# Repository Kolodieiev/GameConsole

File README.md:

Дякую за натхнення проєкту [Лілка v2]([./img/v21.jpg](https://github.com/and3rson/lilka))!

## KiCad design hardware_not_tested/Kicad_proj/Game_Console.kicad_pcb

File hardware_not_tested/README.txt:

Проєкт консолі для ручного виготовлення оптичним лазером або утюжною технологією. Кнопки розміщуються окремо від основної плати на корпусі.
Розмір плати 90*90мм. Теоретична товщина пристрою в корпусі - 35-40мм.

Наразі плата НЕ ТЕСТУВАЛАСЬ!

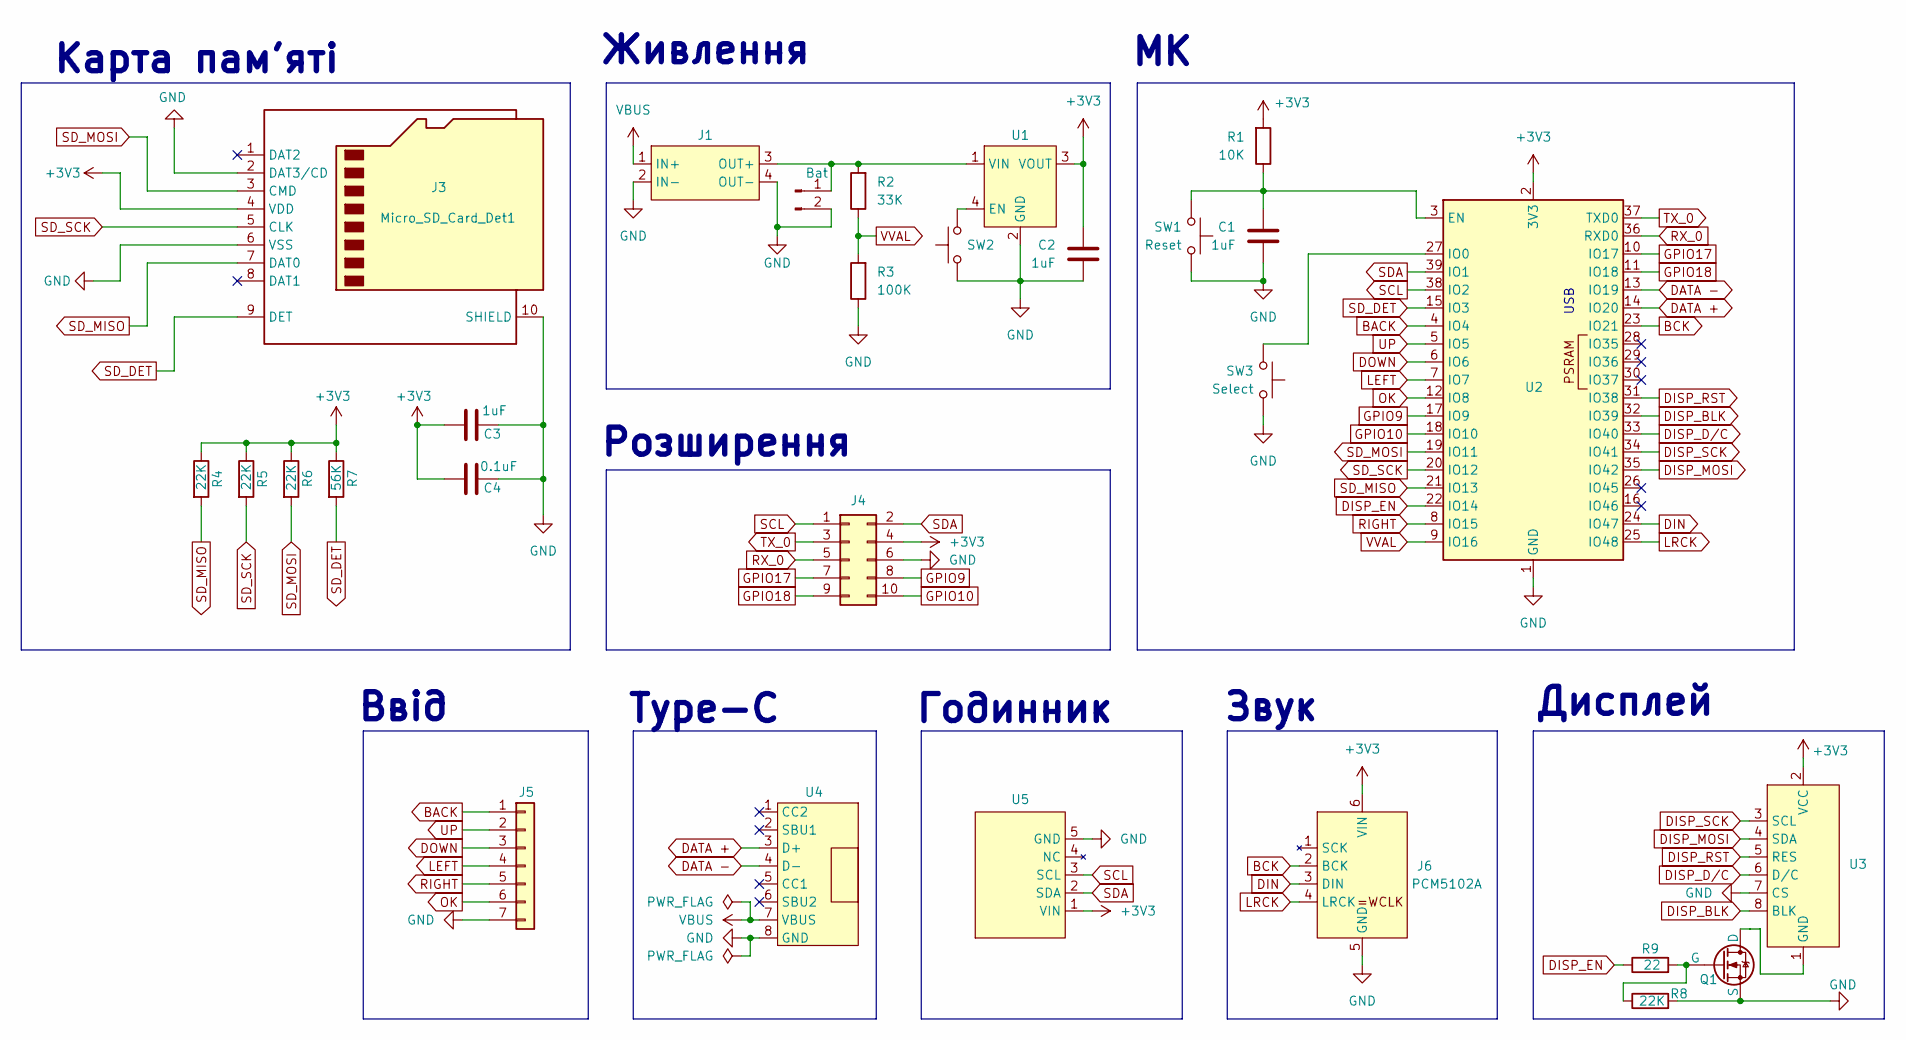
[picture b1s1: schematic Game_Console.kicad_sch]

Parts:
C1, C2, C3: 1uF; C_1206_3216Metric
C4: 0.1uF; C_1206_3216Metric
J1: Charge_Controller_TP4056_WO_Protect
J2: Bat; PinHeader_1x02_P2.54mm_Vertical
J3: Micro_SD_Card_Det1; J_SD_Card-micro_socket_A
J4: Conn_02x05_Odd_Even; PinHeader_2x05_P2.54mm_Vertical
J5: Conn_01x07; PinHeader_1x07_P2.54mm_Vertical
J6: PCM5102A; PCM5102A-I2S-Module
Q1: NMOS; SOT-23
R1: 10K; R_Axial_DIN0204_L3.6mm_D1.6mm_P7.62mm_Horizontal
R2: 33K; R_Axial_DIN0204_L3.6mm_D1.6mm_P7.62mm_Horizontal
R3: 100K; R_Axial_DIN0204_L3.6mm_D1.6mm_P7.62mm_Horizontal
R4, R5, R6, R8: 22K; R_1206_3216Metric
R7: 56K; R_1206_3216Metric
R9: 22; R_1206_3216Metric
SW1: Reset; SW_PUSH_6mm
SW2: SW_Push; PinHeader_1x02_P2.54mm_Vertical
SW3: Select; SW_PUSH_6mm
U1: xl63070_back/boost_module; XL63070_module
U2: ESP32-S3-WROOM-1
U3: IPS_240x320_2_inch
U4: USB TYPE-C to PCB; Connector_Type_C
U5: DS3231SN_module

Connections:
+3V3: C2.1, C3.1, C4.1, J3.4 (VDD), J4.4, J6.6 (VIN), R1.2, R4.1, R5.1, R6.1, R7.1, U1.3 (VOUT), U2.2 (3V3), U3.2 (VCC), U5.1 (VIN)
BACK: J5.1, U2.4 (IO4)
BCK: J6.2 (BCK), U2.23 (IO21)
DATA +: U2.14 (IO20), U4.3 (D+)
DATA -: U2.13 (IO19), U4.4 (D-)
DIN: J6.3 (DIN), U2.24 (IO47)
DISP_BLK: U2.32 (IO39), U3.8 (BLK)
DISP_D/C: U2.33 (IO40), U3.6 (D/C)
DISP_EN: R9.1, U2.22 (IO14)
DISP_MOSI: U2.35 (IO42), U3.4 (SDA)
DISP_RST: U2.31 (IO38), U3.5 (RES)
DISP_SCK: U2.34 (IO41), U3.3 (SCL)
DOWN: J5.3, U2.6 (IO6)
GND: C1.2, C2.2, C3.2, C4.2, J1.2 (IN-), J1.4 (OUT-), J2.2, J3.2 (DAT3/CD), J3.6 (VSS), J3.10 (SHIELD), J4.6, J5.7, J6.5 (GND), Q1.2 (S), R3.1, R8.2, SW1.1, SW2.1, SW3.1, U1.2 (GND), U2.1 (GND), U2.40 (GND), U2.41 (GND), U3.7 (CS), U4.8 (GND), U5.5 (GND)
GPIO9: J4.8, U2.17 (IO9)
GPIO10: J4.10, U2.18 (IO10)
GPIO17: J4.7, U2.10 (IO17)
GPIO18: J4.9, U2.11 (IO18)
LEFT: J5.4, U2.7 (IO7)
LRCK: J6.4 (LRCK), U2.25 (IO48)
unnamed: J1.3 (OUT+), J2.1, R2.2, U1.1 (VIN)
unnamed: Q1.3 (D), U3.1 (GND)
unnamed: Q1.1 (G), R8.1, R9.2
unnamed: SW2.2, U1.4 (EN)
unnamed: C1.1, R1.1, SW1.2, U2.3 (EN)
unnamed: SW3.2, U2.27 (IO0)
OK: J5.6, U2.12 (IO8)
RIGHT: J5.5, U2.8 (IO15)
RX_0: J4.5, U2.36 (RXD0)
SCL: J4.1, U2.38 (IO2), U5.3 (SCL)
SDA: J4.2, U2.39 (IO1), U5.2 (SDA)
SD_DET: J3.9 (DET), R7.2, U2.15 (IO3)
SD_MISO: J3.7 (DAT0), R4.2, U2.21 (IO13)
SD_MOSI: J3.3 (CMD), R6.2, U2.19 (IO11)
SD_SCK: J3.5 (CLK), R5.2, U2.20 (IO12)
TX_0: J4.3, U2.37 (TXD0)
UP: J5.2, U2.5 (IO5)
VBUS: J1.1 (IN+), U4.7 (VBUS)
VVAL: R2.1, R3.2, U2.9 (IO16)

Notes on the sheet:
Карта пам'яті
Годинник
USB
Дисплей
Звук
Розширення
Ввід
Type-C
Живлення

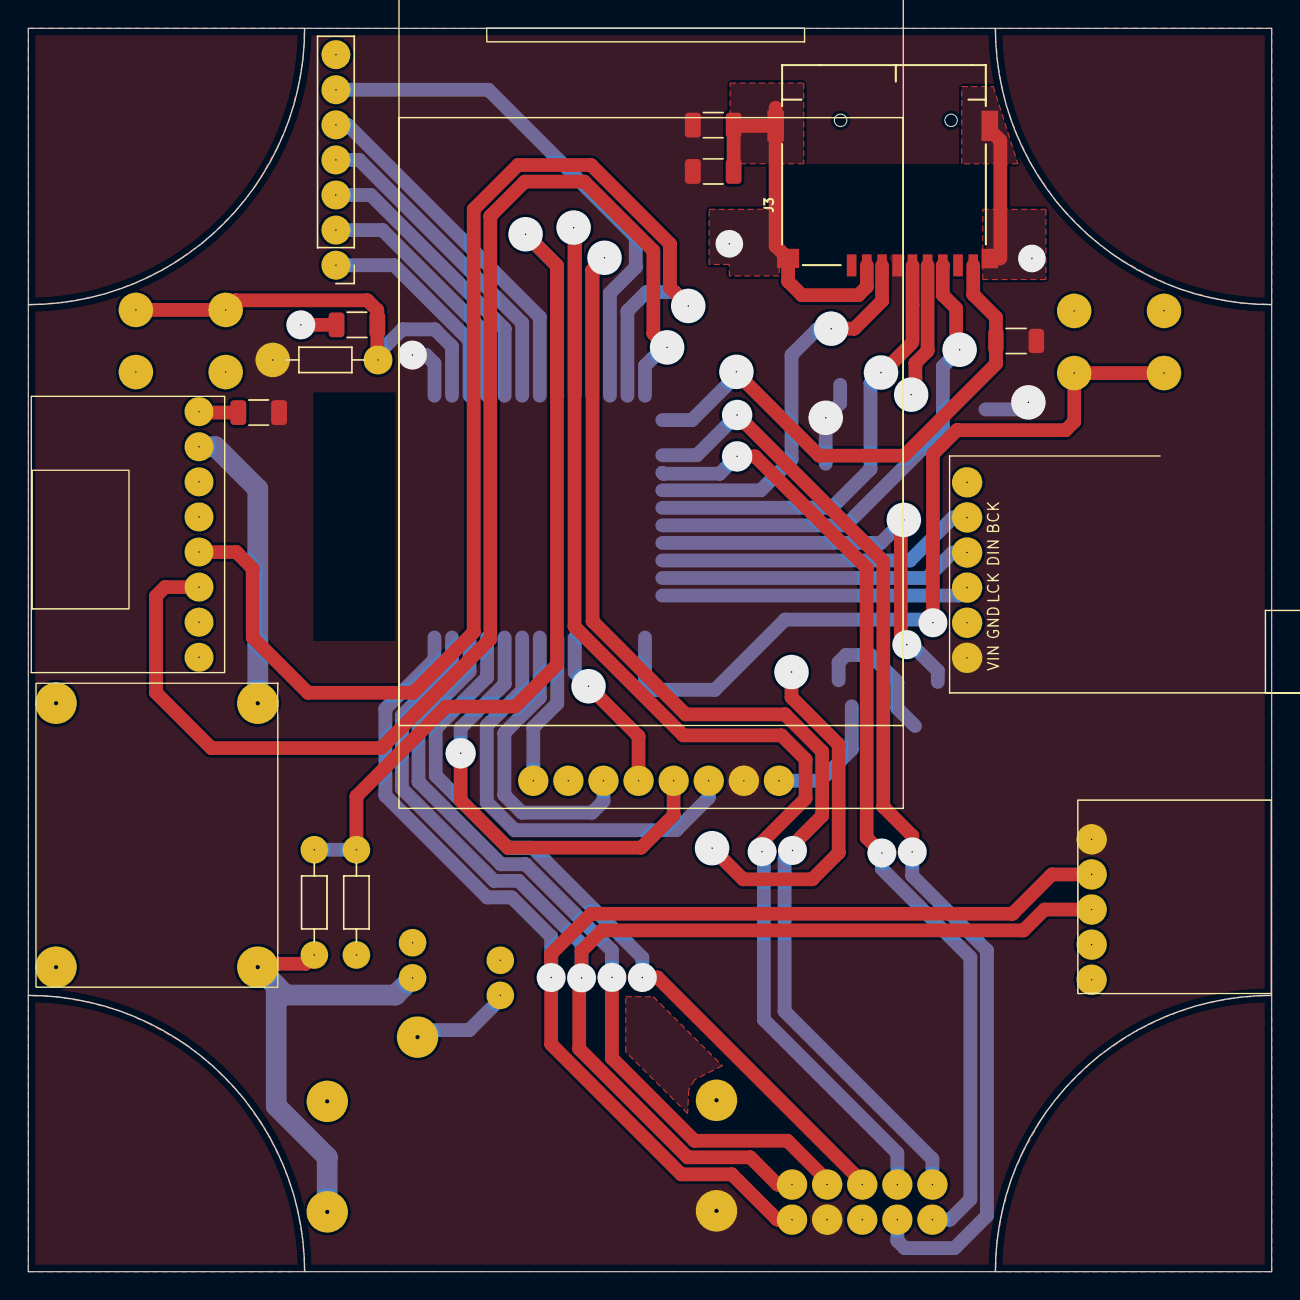
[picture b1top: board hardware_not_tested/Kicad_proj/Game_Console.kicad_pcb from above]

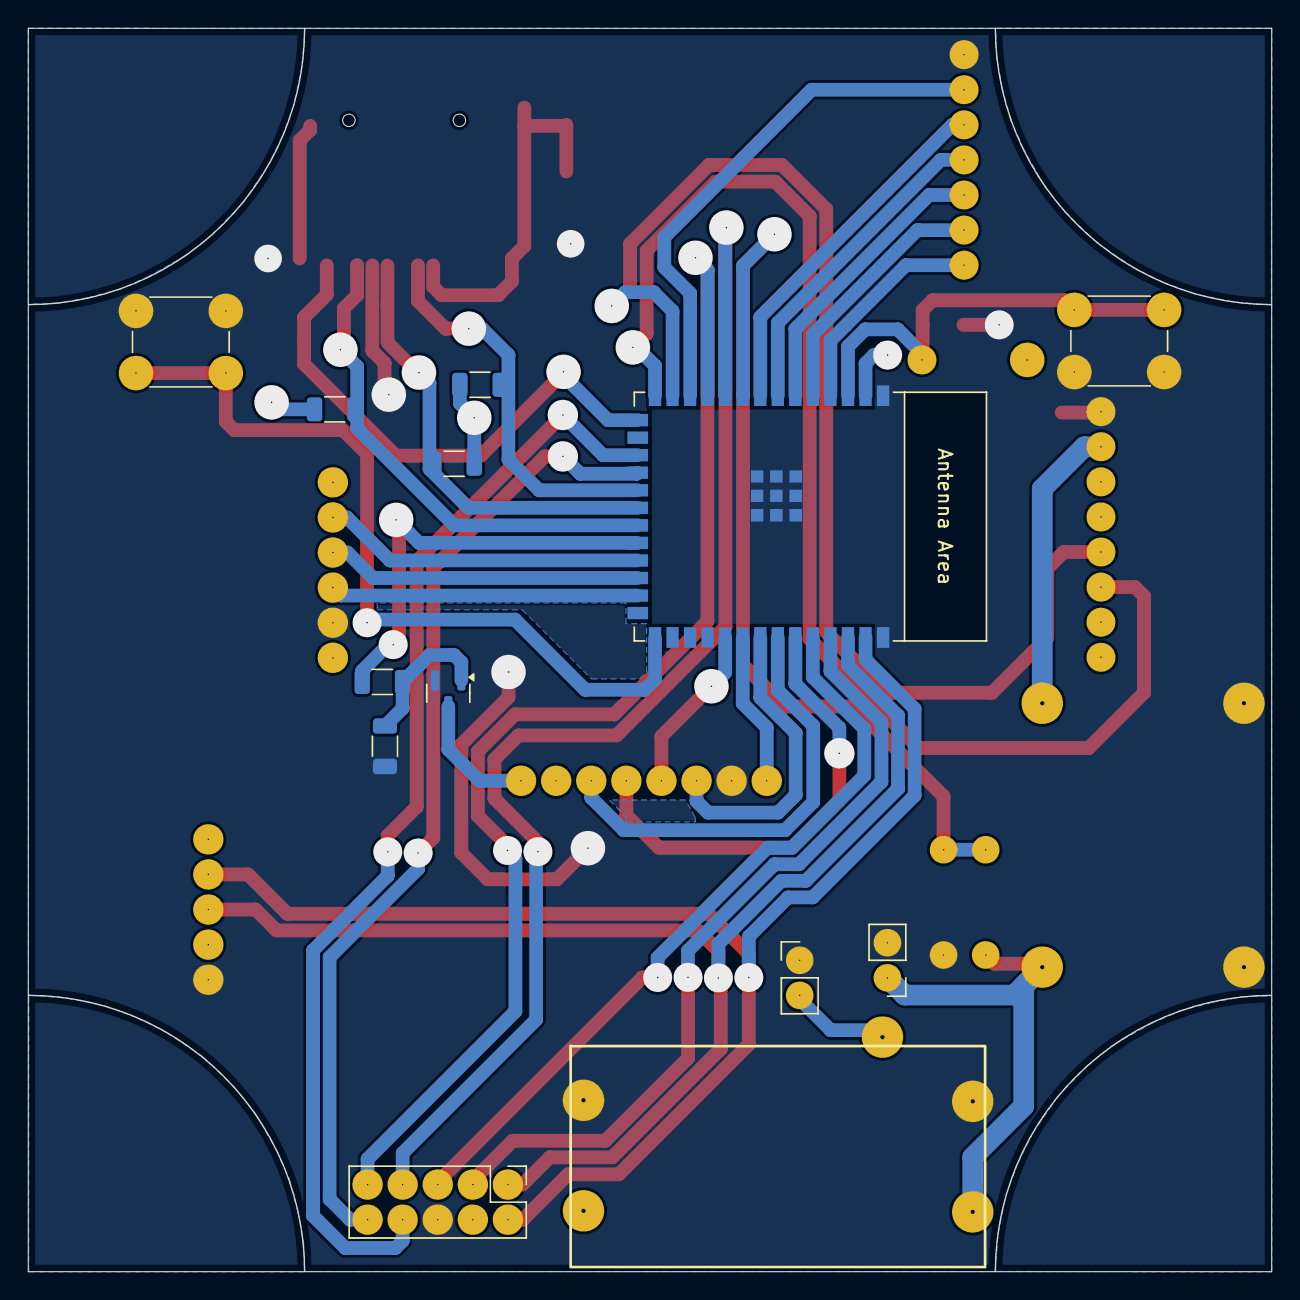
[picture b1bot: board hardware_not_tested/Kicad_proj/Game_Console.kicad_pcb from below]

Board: 2 copper layers, 90.0 x 90.0 mm, 28 parts (13 on the bottom side), 39 nets.

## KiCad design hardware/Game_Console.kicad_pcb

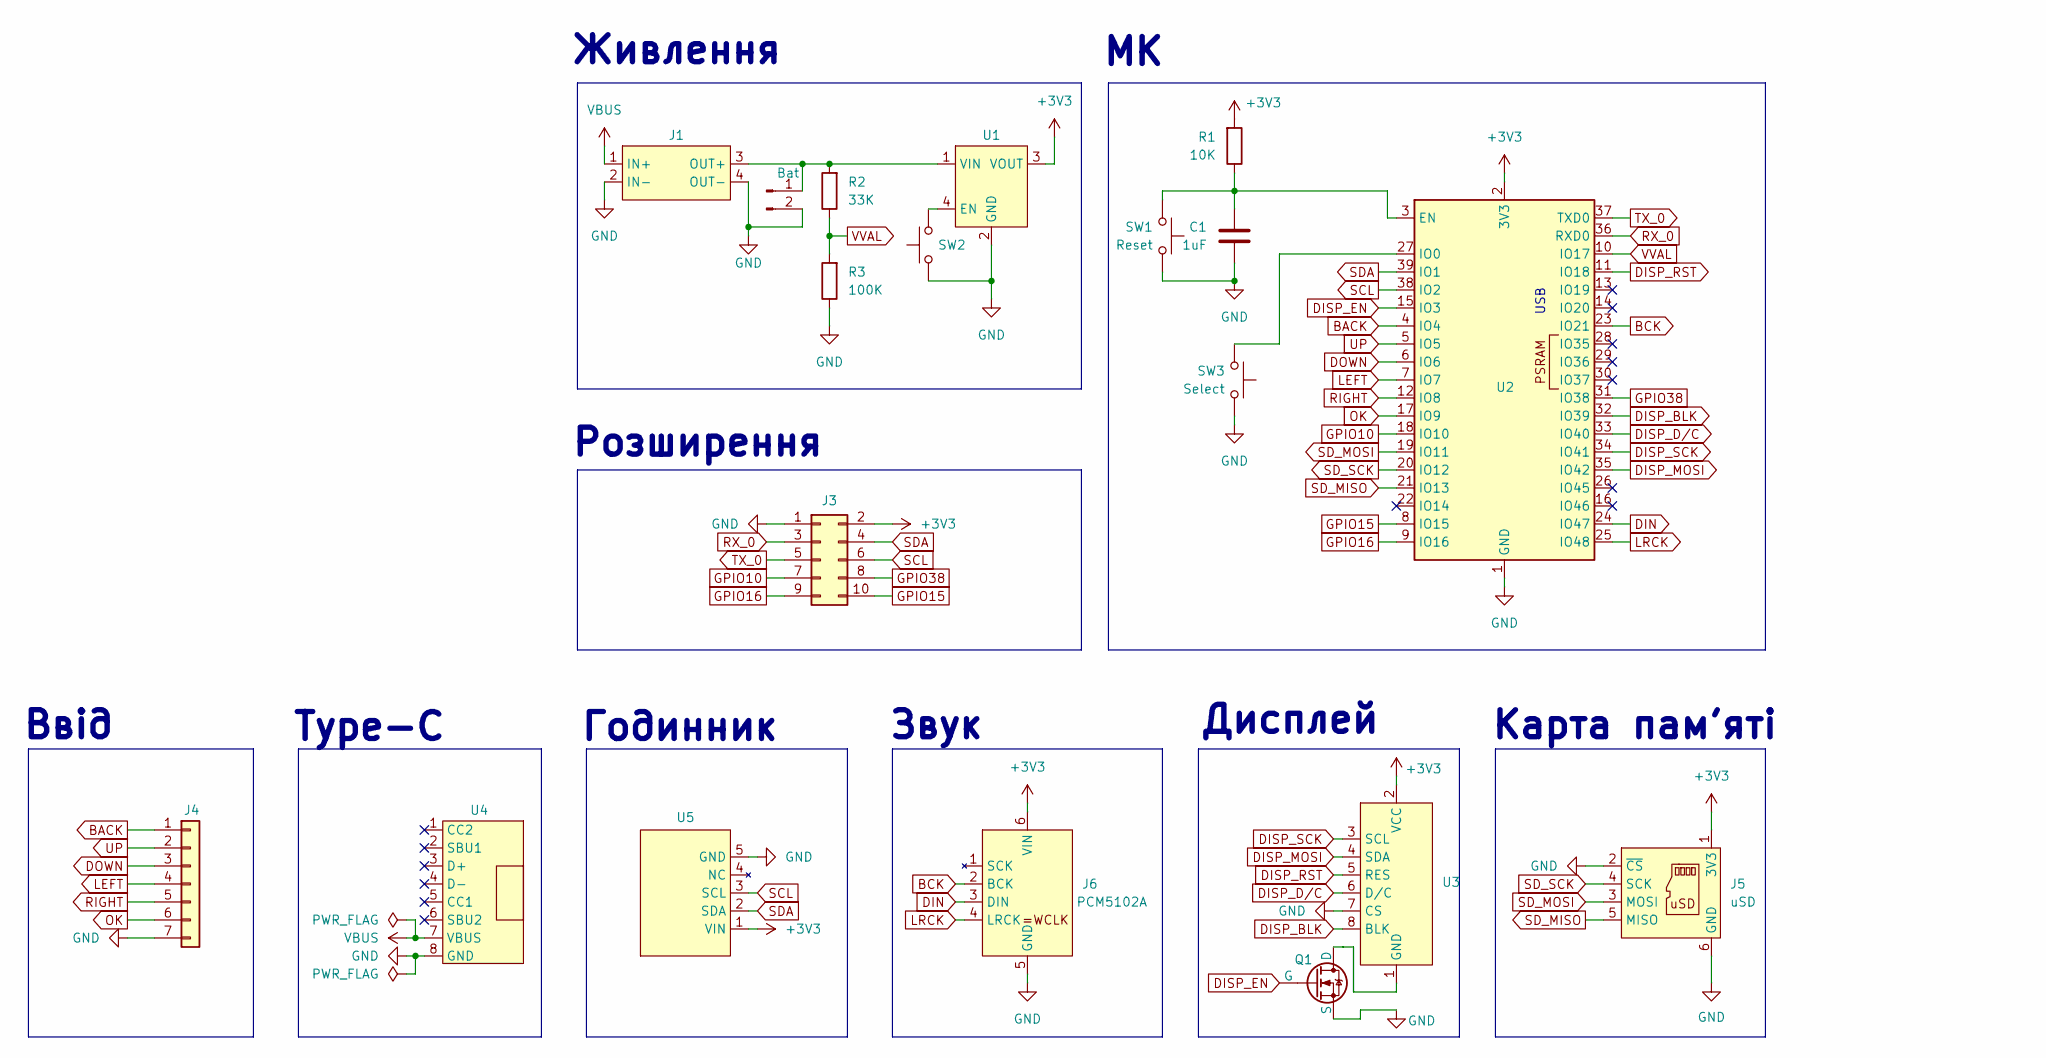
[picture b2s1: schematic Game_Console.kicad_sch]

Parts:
C1: 1uF; C_1206_3216Metric
J1: Charge_Controller_TP4056_WO_Protect
J2: Bat; PinHeader_1x02_P2.54mm_Vertical
J3: Conn_02x05_Odd_Even; PinHeader_2x05_P2.54mm_Vertical
J4: Conn_01x07; PinHeader_1x07_P2.54mm_Vertical
J5: uSD; MicroSD-Adapter-3v3
J6: PCM5102A; PCM5102A-I2S-Module
Q1: NMOS; SOT-23
R1: 10K; R_Axial_DIN0204_L3.6mm_D1.6mm_P7.62mm_Horizontal
R2: 33K; R_Axial_DIN0204_L3.6mm_D1.6mm_P7.62mm_Horizontal
R3: 100K; R_Axial_DIN0204_L3.6mm_D1.6mm_P7.62mm_Horizontal
SW1: Reset; SW_PUSH_6mm
SW2: SW_Push; PinHeader_1x02_P2.54mm_Vertical
SW3: Select; SW_PUSH_6mm
U1: xl63070_back/boost_module; XL63070_module
U2: ESP32-S3-WROOM-1
U3: IPS_240x320_2_inch
U4: USB TYPE-C to PCB; Connector_Type_C
U5: DS3231SN_module

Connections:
+3V3: J3.2, J5.1 (3V3), J6.6 (VIN), R1.2, U1.3 (VOUT), U2.2 (3V3), U3.2 (VCC), U5.1 (VIN)
BACK: J4.1, U2.4 (IO4)
BCK: J6.2 (BCK), U2.23 (IO21)
DIN: J6.3 (DIN), U2.24 (IO47)
DISP_BLK: U2.32 (IO39), U3.8 (BLK)
DISP_D/C: U2.33 (IO40), U3.6 (D/C)
DISP_EN: Q1.1 (G), U2.15 (IO3)
DISP_MOSI: U2.35 (IO42), U3.4 (SDA)
DISP_RST: U2.11 (IO18), U3.5 (RES)
DISP_SCK: U2.34 (IO41), U3.3 (SCL)
DOWN: J4.3, U2.6 (IO6)
GND: C1.2, J1.2 (IN-), J1.4 (OUT-), J2.2, J3.1, J4.7, J5.2 (~CS), J5.6 (GND), J6.5 (GND), Q1.2 (S), R3.1, SW1.1, SW2.1, SW3.1, U1.2 (GND), U2.1 (GND), U2.40 (GND), U2.41 (GND), U3.7 (CS), U4.8 (GND), U5.5 (GND)
GPIO10: J3.7, U2.18 (IO10)
GPIO15: J3.10, U2.8 (IO15)
GPIO16: J3.9, U2.9 (IO16)
GPIO38: J3.8, U2.31 (IO38)
LEFT: J4.4, U2.7 (IO7)
LRCK: J6.4 (LRCK), U2.25 (IO48)
unnamed: J1.3 (OUT+), J2.1, R2.2, U1.1 (VIN)
unnamed: Q1.3 (D), U3.1 (GND)
unnamed: SW2.2, U1.4 (EN)
unnamed: C1.1, R1.1, SW1.2, U2.3 (EN)
unnamed: SW3.2, U2.27 (IO0)
OK: J4.6, U2.17 (IO9)
RIGHT: J4.5, U2.12 (IO8)
RX_0: J3.3, U2.36 (RXD0)
SCL: J3.6, U2.38 (IO2), U5.3 (SCL)
SDA: J3.4, U2.39 (IO1), U5.2 (SDA)
SD_MISO: J5.5 (MISO), U2.21 (IO13)
SD_MOSI: J5.3 (MOSI), U2.19 (IO11)
SD_SCK: J5.4 (SCK), U2.20 (IO12)
TX_0: J3.5, U2.37 (TXD0)
UP: J4.2, U2.5 (IO5)
VBUS: J1.1 (IN+), U4.7 (VBUS)
VVAL: R2.1, R3.2, U2.10 (IO17)

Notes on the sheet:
Карта пам'яті
Годинник
USB
Дисплей
Звук
Розширення
Ввід
Type-C
Живлення

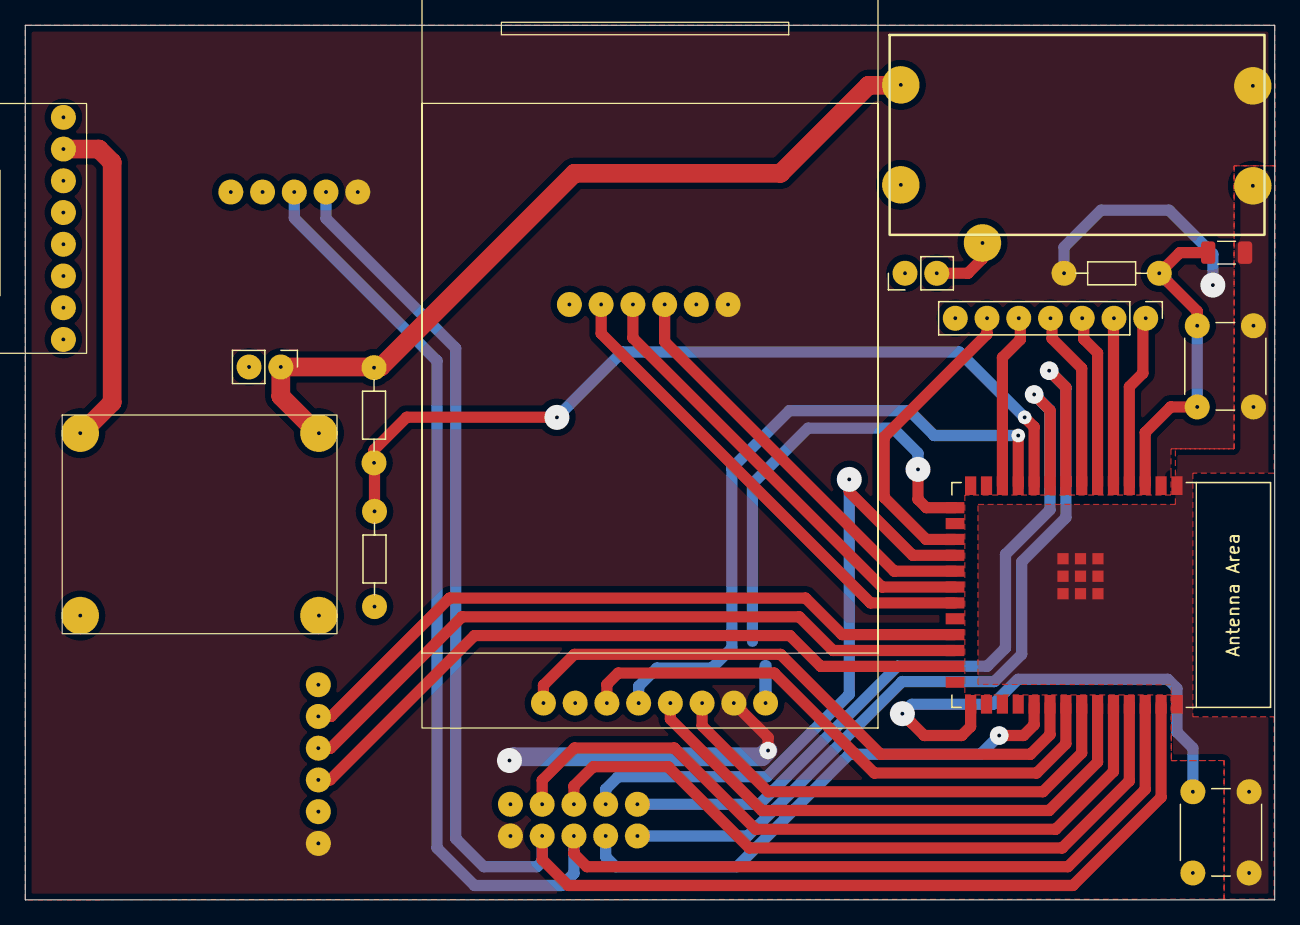
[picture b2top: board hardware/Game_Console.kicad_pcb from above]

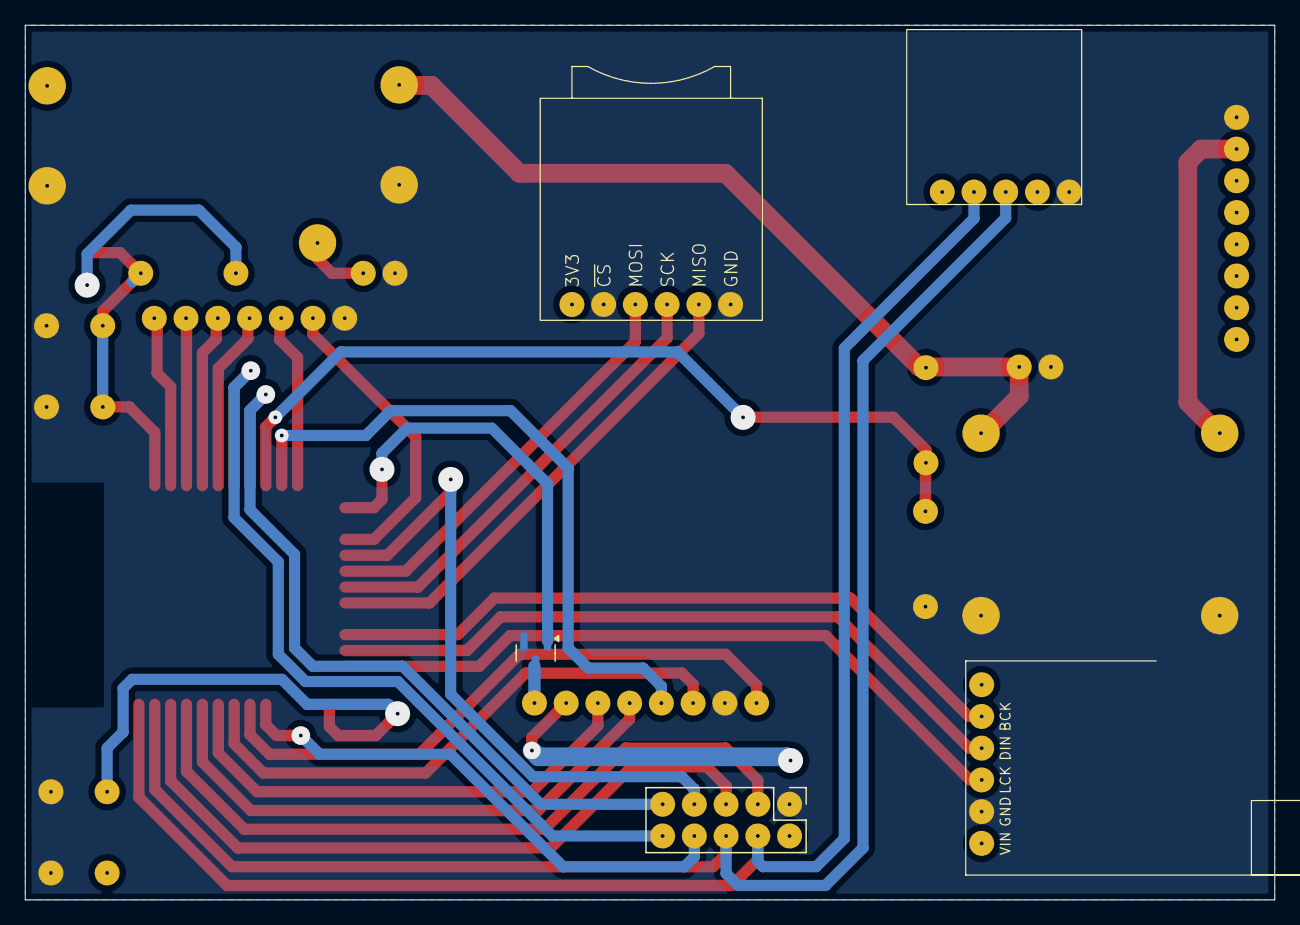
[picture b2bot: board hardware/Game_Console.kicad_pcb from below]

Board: 2 copper layers, 100.0 x 70.0 mm, 19 parts (5 on the bottom side), 35 nets.

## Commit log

2024-06-17 Додано ресурси
    Ресурси, які можуть бути використані в майбутньому
2024-06-20 Update Audio
2024-06-23 Підтримка вимкнення окремих кнопок
2024-06-23 Можливість глобально вимкнути відрисовку
2024-06-23 Фікс проблемних місць
2024-06-27 Некоректне опрацювання unicode
2024-06-27 Оптимізація
2024-06-27 Помилка логування
2024-06-27 Додано читалку txt файлів
2024-06-28 Зменшення енергоспоживання в очікуванні
2024-06-29 Конвертер fb2 в txt
2024-06-29 Некоректне зчитування списку каталогів
2024-07-01 Додано обробку символу "тире"
2024-07-05 Рефакторинг
2024-07-05 Некоректне закриття файлів
2024-07-06 Виправлено некоректне продовження треку
2024-07-09 Оптимізовано визначення алфавіту
2024-07-21 Некоректна обробка new
2024-07-26 Add bk1198 chip
2024-08-21 Виправлення для ESP32
2024-08-21 Update bk1198
2024-09-22 Некоректне відображення значення
2024-09-28 Приховано метод setText
2024-10-06 Додано дерективу оптимізації
2024-10-07 Некоректна ініціалізація
2024-10-08 Enable optimization
2024-10-22 Налаштування екрану ESP32-3248S035
2024-10-22 Update ESP32-3248S035 setup
2024-10-22 Винесено налаштування
    Налаштування фреймворку винесено в окремий розділ
2024-10-22 Підтримка сенсорної панелі
2024-10-22 Підтримка драйвера GT911
2024-10-22 Підтримка 1 бітної палітри
2024-10-22 Виправлено ім'я методу
2024-10-22 Прибрано віртуальність методів
2024-10-22 Прибрано модифікатор inline
2024-10-22 Додано підтримку сенсорного екрану
2024-10-22 Виправлено опис методів
2024-10-22 Оптимізація пошуку
2024-10-22 Переміщено файл класу IWidgetContainer
2024-10-24 Виправлено ім'я змінної
2024-10-24 Виправлено обробку натискань
2024-10-25 Виправлено помилку
2024-10-29 Відокремлено налаштування sd
2024-10-29 Відокремлено налаштування sd spi
2024-11-05 Додано бібліотеку для генерації QR
2024-11-05 Додано бібліотеку файлового web-серверу
2024-11-05 Додано бібліотеку асинхронного web-серверу
2024-11-10 Додано обгортку для генератора QR
2024-11-17 Рівень логування
2024-11-17 Додано керування SPI
2024-11-17 Покращено управління SD-картою
2024-11-17 Виправлено помилки
2024-11-17 Поліпшення та виправлення
2024-11-17 Додано шаблон
2024-11-17 Незначні оновлення
2024-11-17 Переміщено
2024-11-17 Оптимізація. Рефакторинг.
2024-11-17 Синхронізація відрисовки
    Виправлені помилки синхронізації відрисовки під час оновлення UI з інших потоків
2024-11-17 Відокремлення налаштувань дисплею
2024-11-17 Налаштування i2s
2024-11-17 Помилка керування відрисовкою
2024-11-17 Виправлення синхронізації відрисовки
2024-11-17 Покращення керування підсвіткою
2024-11-17 Оновлення
2024-11-17 Перевірка SD карти
2024-11-17 Виправлення помилок
2024-11-17 Екран налаштування файлового серверу
2024-11-18 Відокремлено формування клавіатури
2024-11-18 Відсутнє встановлення флагу
2024-11-19 Виправлення
2024-11-19 Допрацьовано
2024-11-19 Нові рядки
2024-11-20 Виправлено час затримки після натискання
2024-11-20 Додано нагадування
2024-11-20 Виправлено відзеркалення
2024-11-29 Переміщено ScreenManager
2024-11-29 Покращено синхронізацію
2024-12-02 Некоректне створення каталогу налаштувань
2024-12-02 Переміщено в namespace
2024-12-02 Перейменовано константу
2024-12-02 Оптимізація використання RAM
2024-12-02 Зменшено кількість RAM для UI
2024-12-09 Синхронізовано із фреймворком
2024-12-09 Синхронізація
2024-12-10 Зациклення для контекстного меню
2025-01-05 Оновлення GUI
2025-01-07 Перейменовано IScreen на IContext
    Аби запобігти плутанині IScreen з фізичним пристроєм для відображення зображення, його було перейменовано. Окрім того, ім'я IContext більш точно передає сутність типу.
2025-01-11 Додано посадкове місце сокету SD.
2025-01-11 Зменшено час запуску
2025-01-11 Додано повідомлення про результат
2025-01-11 Виправлено некоректну відрисовку
2025-01-14 Консоль з виправленими недоліками
